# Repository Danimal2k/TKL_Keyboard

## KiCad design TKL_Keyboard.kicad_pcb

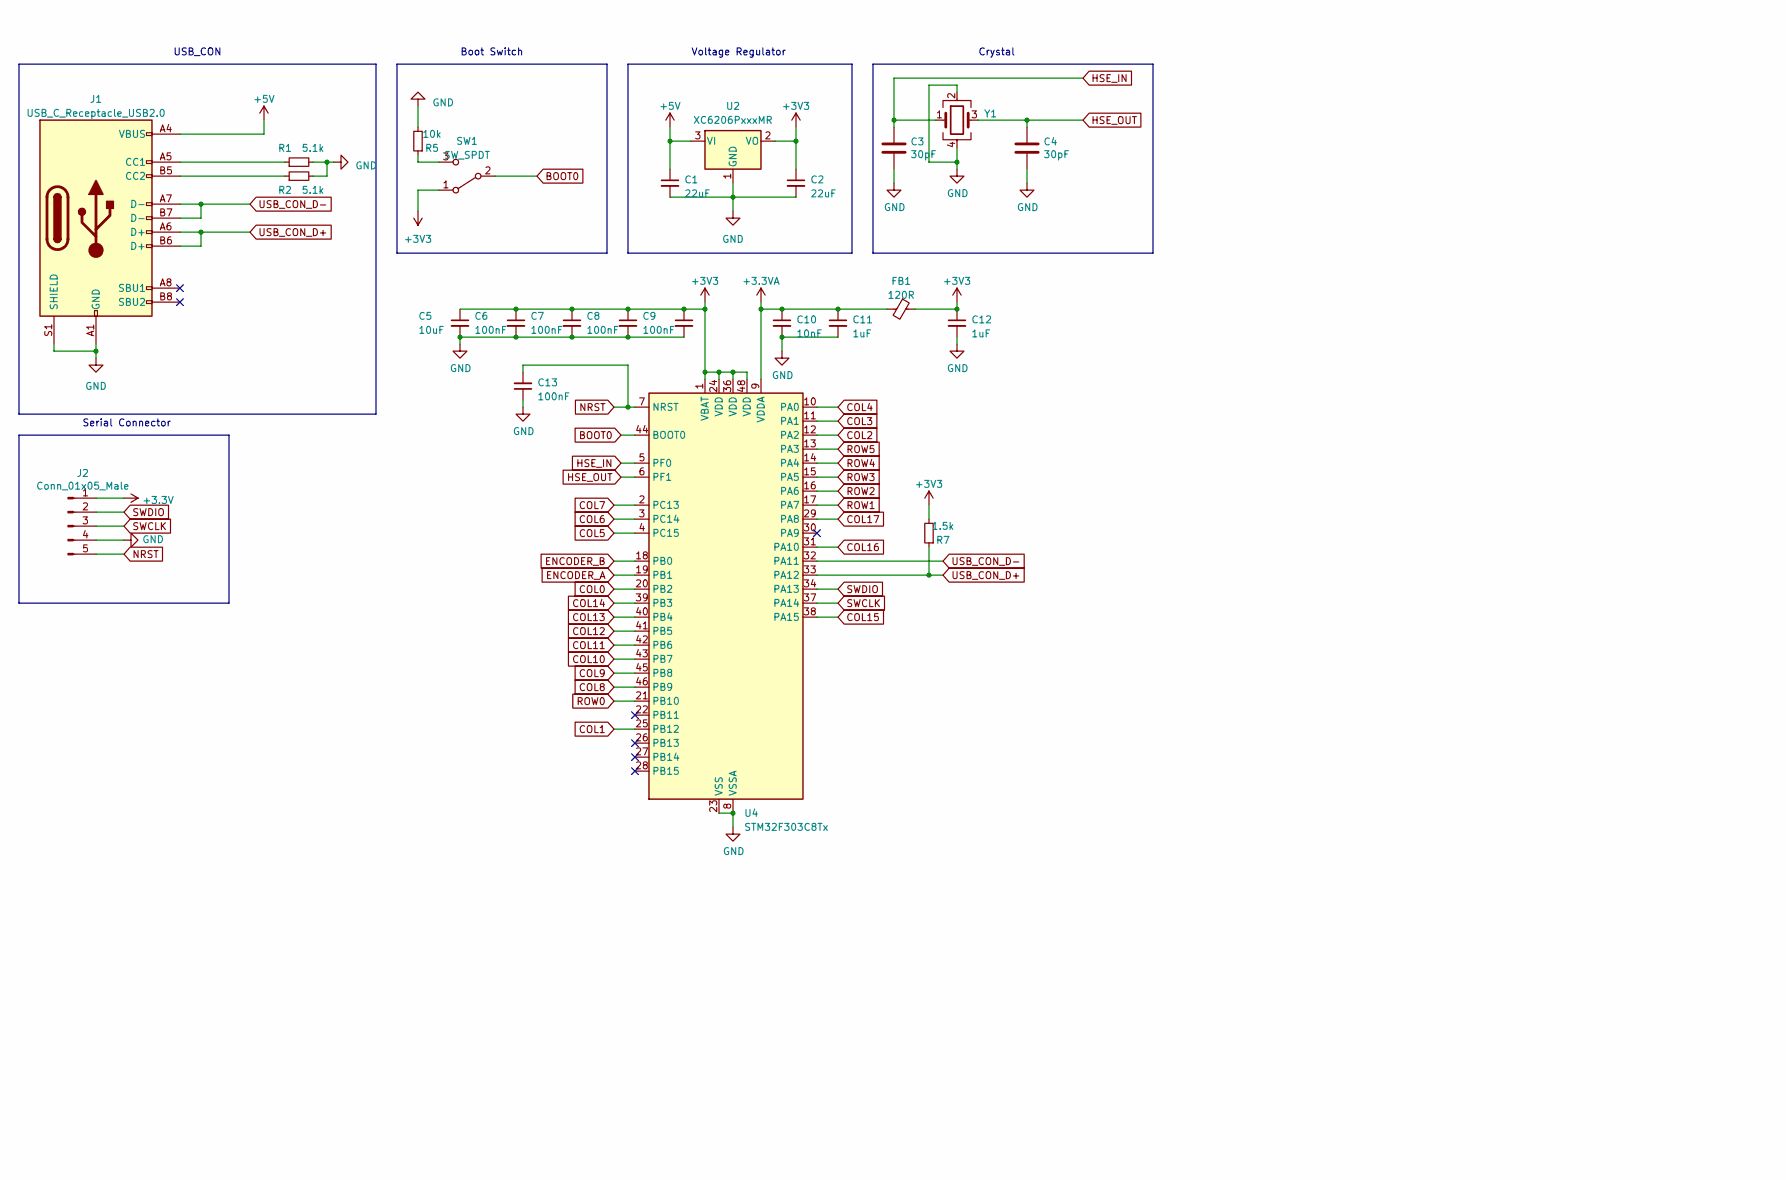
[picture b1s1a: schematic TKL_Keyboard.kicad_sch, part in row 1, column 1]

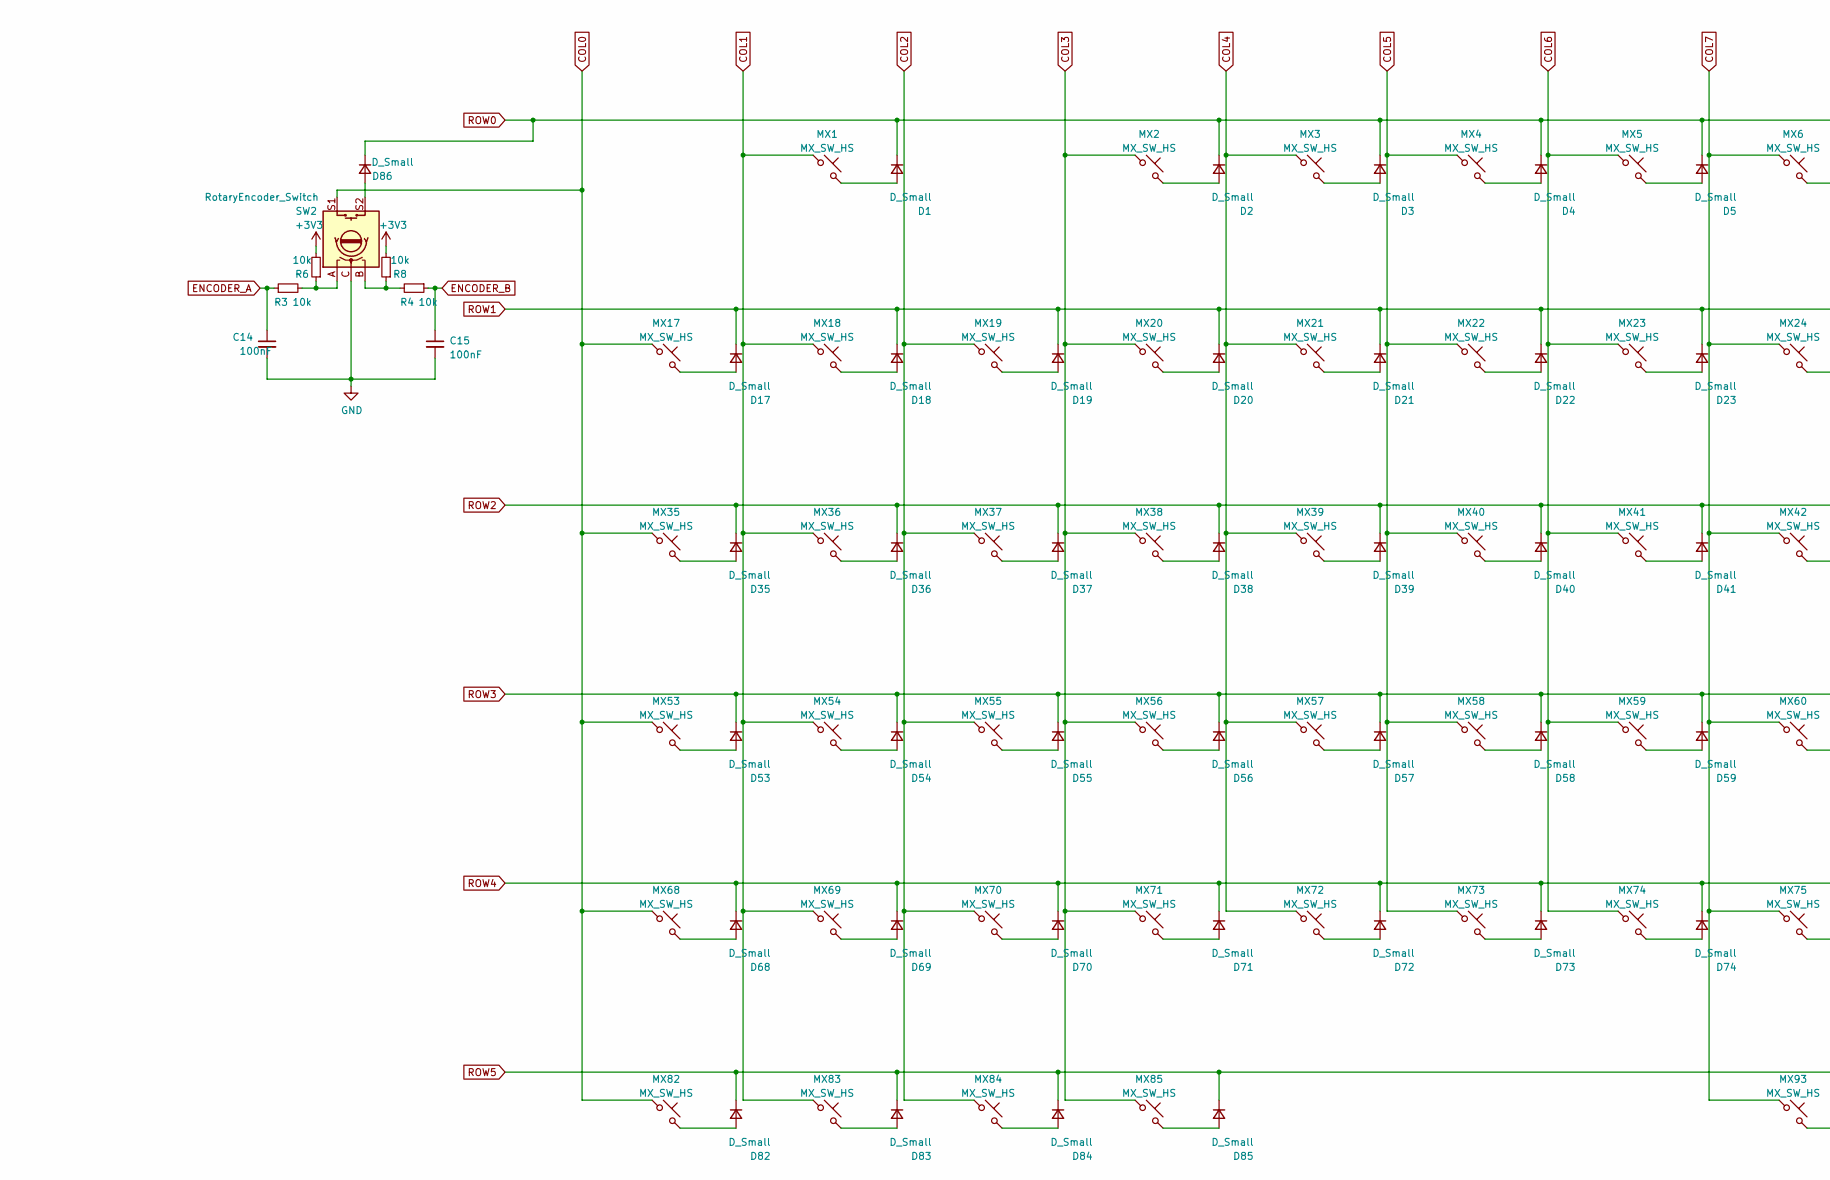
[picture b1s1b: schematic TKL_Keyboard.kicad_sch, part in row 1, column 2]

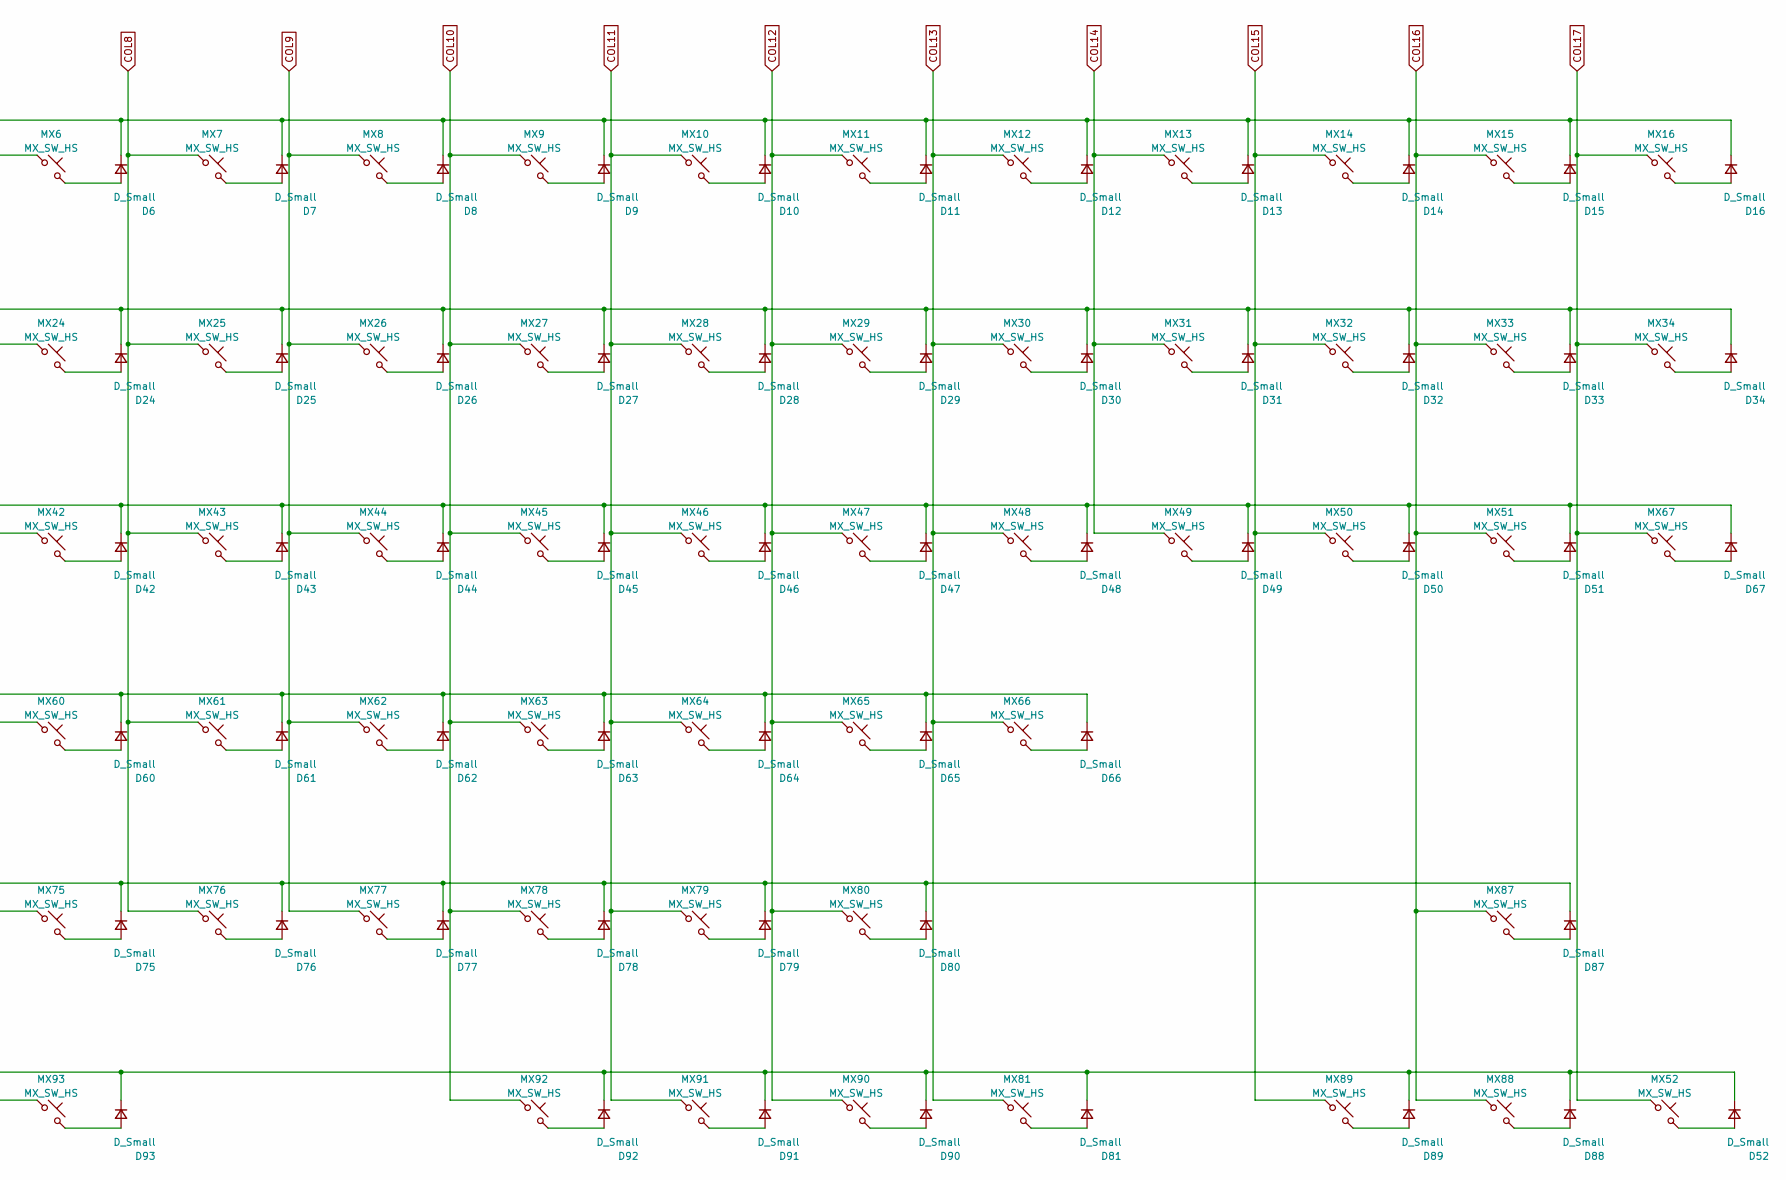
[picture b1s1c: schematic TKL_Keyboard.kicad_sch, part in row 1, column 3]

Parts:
C1, C2: 22uF; C_0805_2012Metric
C3, C4: 30pF; C_0402_1005Metric; LCSC PN C22397
C5: 10uF; C_0805_2012Metric
C6, C7, C8, C9, C13, C14, C15: 100nF; C_0402_1005Metric
C10: 10nF; C_0402_1005Metric
C11, C12: 1uF; C_0402_1005Metric
D1, D2, D3, D4, D5, D6, D7, D8, D9, D10, D11, D12, D13, D14, D15, D16, D17, D18, D19, D20, D21, D22, D23, D24, D25, D26, D27, D28, D29, D30, D31, D32, D33, D34, D35, D36, D37, D38, D39, D40, D41, D42, D43, D44, D45, D46, D47, D48, D49, D50, D51, D52, D53, D54, D55, D56, D57, D58, D59, D60, D61, D62, D63, D64, D65, D66, D67, D68, D69, D70, D71, D72, D73, D74, D75, D76, D77, D78, D79, D80, D81, D82, D83, D84, D85, D86, D87, D88, D89, D90, D91, D92, D93: D_Small; D_SOD-123
FB1: 120R; L_0603_1608Metric
J1: USB_C_Receptacle_USB2.0; USB_C_Receptacle_GCT_USB4085_CUSTOM
J2: Conn_01x05_Male; PinHeader_1x05_P2.54mm_Vertical
MX1, MX2, MX3, MX4, MX5, MX6, MX7, MX8, MX9, MX10, MX11, MX12, MX13, MX14, MX15, MX16, MX17, MX18, MX19, MX20, MX21, MX22, MX23, MX24, MX25, MX26, MX27, MX28, MX29, MX30, MX32, MX33, MX34, MX35, MX36, MX37, MX38, MX39, MX40, MX41, MX42, MX43, MX44, MX45, MX46, MX47, MX48, MX49, MX50, MX51, MX52, MX53, MX54, MX55, MX56, MX57, MX58, MX59, MX60, MX61, MX62, MX63, MX64, MX65, MX67, MX68, MX70, MX71, MX72, MX73, MX74, MX75, MX76, MX77, MX78, MX79, MX81, MX82, MX83, MX84, MX85, MX87, MX88, MX89, MX90, MX91, MX92: MX_SW_HS; MXOnly-1U-Hotswap
MX31: MX_SW_HS; MXOnly-2U-Hotswap
MX66, MX69: MX_SW_HS; MXOnly-2.25U-Hotswap
MX80: MX_SW_HS; MXOnly-2.75U-Hotswap
MX93: MX_SW_HS; MXOnly-6.25U-Hotswap-ReversedStabilizers
R1, R2: 5.1k; R_0805_2012Metric
R3, R4, R5, R6, R8: 10k; R_0805_2012Metric
R7: 1.5k; R_0805_2012Metric
SW1: SW_SPDT; SW_SPDT_PCM12
SW2: RotaryEncoder_Switch; RotaryEncoder_Alps_EC11E-Switch_Vertical_H20mm
U2: XC6206PxxxMR; SOT-23-3
U4: STM32F303C8Tx; LQFP-48_7x7mm_P0.5mm
Y1: 16MHz; Crystal_SMD_5032-4Pin_5.0x3.2mm; LCSC PN C133333

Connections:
+3.3VA: C10.1, C11.1, FB1.2, U4.9 (VDDA)
+5V: C1.1, J1.A4 (VBUS), J1.A9 (VBUS), J1.B4 (VBUS), J1.B9 (VBUS), U2.3 (VI)
BOOT0: SW1.2 (B), U4.44 (BOOT0)
COL0: MX17.1, MX35.1, MX53.1, MX68.1, MX82.1, SW2.S1, U4.20 (PB2)
COL1: MX1.1, MX18.1, MX36.1, MX54.1, MX69.1, MX83.1, U4.25 (PB12)
COL2: MX19.1, MX37.1, MX55.1, MX70.1, MX84.1, U4.12 (PA2)
COL3: MX2.1, MX20.1, MX38.1, MX56.1, MX71.1, MX85.1, U4.11 (PA1)
COL4: MX3.1, MX21.1, MX39.1, MX57.1, MX72.1, U4.10 (PA0)
COL5: MX4.1, MX22.1, MX40.1, MX58.1, MX73.1, U4.4 (PC15)
COL6: MX5.1, MX23.1, MX41.1, MX59.1, MX74.1, U4.3 (PC14)
COL7: MX6.1, MX24.1, MX42.1, MX60.1, MX75.1, MX93.1, U4.2 (PC13)
COL8: MX7.1, MX25.1, MX43.1, MX61.1, MX76.1, U4.46 (PB9)
COL9: MX8.1, MX26.1, MX44.1, MX62.1, MX77.1, U4.45 (PB8)
COL10: MX9.1, MX27.1, MX45.1, MX63.1, MX78.1, MX92.1, U4.43 (PB7)
COL11: MX10.1, MX28.1, MX46.1, MX64.1, MX79.1, MX91.1, U4.42 (PB6)
COL12: MX11.1, MX29.1, MX47.1, MX65.1, MX80.1, MX90.1, U4.41 (PB5)
COL13: MX12.1, MX30.1, MX48.1, MX66.1, MX81.1, U4.40 (PB4)
COL14: MX13.1, MX31.1, MX49.1, U4.39 (PB3)
COL15: MX14.1, MX32.1, MX50.1, MX89.1, U4.38 (PA15)
COL16: MX15.1, MX33.1, MX51.1, MX87.1, MX88.1, U4.31 (PA10)
COL17: MX16.1, MX34.1, MX52.1, MX67.1, U4.29 (PA8)
ENCODER_A: C14.1, R3.1, U4.19 (PB1)
ENCODER_B: C15.1, R4.1, U4.18 (PB0)
GND: C1.2, C2.2, C3.2, C4.2, C5.2, C6.2, C7.2, C8.2, C9.2, C10.2, C11.2, C12.2, C13.1, C14.2, C15.2, J1.A1 (GND), J1.A12 (GND), J1.B1 (GND), J1.B12 (GND), J1.S1 (SHIELD), J2.4, R1.2, R2.2, R5.2, SW2.C, U2.1 (GND), U4.8 (VSSA), U4.23 (VSS), U4.35 (VSS), U4.47 (VSS), Y1.2, Y1.4
HSE_IN: C3.1, U4.5 (PF0), Y1.1
HSE_OUT: C4.1, U4.6 (PF1), Y1.3
NRST: C13.2, J2.5, U4.7 (NRST)
unnamed: D1.2 (A), MX1.2
unnamed: D2.2 (A), MX2.2
unnamed: D3.2 (A), MX3.2
unnamed: D4.2 (A), MX4.2
unnamed: D5.2 (A), MX5.2
unnamed: D6.2 (A), MX6.2
unnamed: D7.2 (A), MX7.2
unnamed: D8.2 (A), MX8.2
unnamed: D9.2 (A), MX9.2
unnamed: D10.2 (A), MX10.2
unnamed: D11.2 (A), MX11.2
unnamed: D12.2 (A), MX12.2
unnamed: D13.2 (A), MX13.2
unnamed: D14.2 (A), MX14.2
unnamed: D15.2 (A), MX15.2
unnamed: D16.2 (A), MX16.2
unnamed: D17.2 (A), MX17.2
unnamed: D18.2 (A), MX18.2
unnamed: D19.2 (A), MX19.2
unnamed: D20.2 (A), MX20.2
unnamed: D21.2 (A), MX21.2
unnamed: D22.2 (A), MX22.2
unnamed: D23.2 (A), MX23.2
unnamed: D24.2 (A), MX24.2
unnamed: D25.2 (A), MX25.2
unnamed: D26.2 (A), MX26.2
unnamed: D27.2 (A), MX27.2
unnamed: D28.2 (A), MX28.2
unnamed: D29.2 (A), MX29.2
unnamed: D30.2 (A), MX30.2
unnamed: D31.2 (A), MX31.2
unnamed: D32.2 (A), MX32.2
unnamed: D33.2 (A), MX33.2
unnamed: D34.2 (A), MX34.2
unnamed: D35.2 (A), MX35.2
unnamed: D36.2 (A), MX36.2
unnamed: D37.2 (A), MX37.2
unnamed: D38.2 (A), MX38.2
unnamed: D39.2 (A), MX39.2
unnamed: D40.2 (A), MX40.2
unnamed: D41.2 (A), MX41.2
unnamed: D42.2 (A), MX42.2
unnamed: D43.2 (A), MX43.2
unnamed: D44.2 (A), MX44.2
unnamed: D45.2 (A), MX45.2
unnamed: D46.2 (A), MX46.2
unnamed: D47.2 (A), MX47.2
unnamed: D48.2 (A), MX48.2
unnamed: D49.2 (A), MX49.2
unnamed: D50.2 (A), MX50.2
unnamed: D51.2 (A), MX51.2
unnamed: D52.2 (A), MX52.2
unnamed: D53.2 (A), MX53.2
unnamed: D54.2 (A), MX54.2
unnamed: D55.2 (A), MX55.2
unnamed: D56.2 (A), MX56.2
unnamed: D57.2 (A), MX57.2
unnamed: D58.2 (A), MX58.2
unnamed: D59.2 (A), MX59.2
unnamed: D60.2 (A), MX60.2
unnamed: D61.2 (A), MX61.2
unnamed: D62.2 (A), MX62.2
unnamed: D63.2 (A), MX63.2
unnamed: D64.2 (A), MX64.2
unnamed: D65.2 (A), MX65.2
unnamed: D66.2 (A), MX66.2
unnamed: D67.2 (A), MX67.2
unnamed: D68.2 (A), MX68.2
unnamed: D69.2 (A), MX69.2
unnamed: D70.2 (A), MX70.2
unnamed: D71.2 (A), MX71.2
unnamed: D72.2 (A), MX72.2
unnamed: D73.2 (A), MX73.2
unnamed: D74.2 (A), MX74.2
unnamed: D75.2 (A), MX75.2
unnamed: D76.2 (A), MX76.2
unnamed: D77.2 (A), MX77.2
unnamed: D78.2 (A), MX78.2
unnamed: D79.2 (A), MX79.2
unnamed: D80.2 (A), MX80.2
unnamed: D81.2 (A), MX81.2
unnamed: D82.2 (A), MX82.2
unnamed: D83.2 (A), MX83.2
unnamed: D84.2 (A), MX84.2
unnamed: D85.2 (A), MX85.2
unnamed: D86.2 (A), SW2.S2
unnamed: D87.2 (A), MX87.2
unnamed: D88.2 (A), MX88.2
unnamed: D89.2 (A), MX89.2
unnamed: D90.2 (A), MX90.2
unnamed: D91.2 (A), MX91.2
unnamed: D92.2 (A), MX92.2
unnamed: D93.2 (A), MX93.2
unnamed: J1.A5 (CC1), R1.1
unnamed: J1.B5 (CC2), R2.1
unnamed: R3.2, R6.1, SW2.A
unnamed: R4.2, R8.1, SW2.B
unnamed: R5.1, SW1.3 (C)
ROW0: D1.1 (K), D2.1 (K), D3.1 (K), D4.1 (K), D5.1 (K), D6.1 (K), D7.1 (K), D8.1 (K), D9.1 (K), D10.1 (K), D11.1 (K), D12.1 (K), D13.1 (K), D14.1 (K), D15.1 (K), D16.1 (K), D86.1 (K), U4.21 (PB10)
ROW1: D17.1 (K), D18.1 (K), D19.1 (K), D20.1 (K), D21.1 (K), D22.1 (K), D23.1 (K), D24.1 (K), D25.1 (K), D26.1 (K), D27.1 (K), D28.1 (K), D29.1 (K), D30.1 (K), D31.1 (K), D32.1 (K), D33.1 (K), D34.1 (K), U4.17 (PA7)
ROW2: D35.1 (K), D36.1 (K), D37.1 (K), D38.1 (K), D39.1 (K), D40.1 (K), D41.1 (K), D42.1 (K), D43.1 (K), D44.1 (K), D45.1 (K), D46.1 (K), D47.1 (K), D48.1 (K), D49.1 (K), D50.1 (K), D51.1 (K), D67.1 (K), U4.16 (PA6)
ROW3: D53.1 (K), D54.1 (K), D55.1 (K), D56.1 (K), D57.1 (K), D58.1 (K), D59.1 (K), D60.1 (K), D61.1 (K), D62.1 (K), D63.1 (K), D64.1 (K), D65.1 (K), D66.1 (K), U4.15 (PA5)
ROW4: D68.1 (K), D69.1 (K), D70.1 (K), D71.1 (K), D72.1 (K), D73.1 (K), D74.1 (K), D75.1 (K), D76.1 (K), D77.1 (K), D78.1 (K), D79.1 (K), D80.1 (K), D87.1 (K), U4.14 (PA4)
ROW5: D52.1 (K), D81.1 (K), D82.1 (K), D83.1 (K), D84.1 (K), D85.1 (K), D88.1 (K), D89.1 (K), D90.1 (K), D91.1 (K), D92.1 (K), D93.1 (K), U4.13 (PA3)
SWCLK: J2.3, U4.37 (PA14)
SWDIO: J2.2, U4.34 (PA13)
USB_CON_D+: J1.A6 (D+), J1.B6 (D+), R7.1, U4.33 (PA12)
USB_CON_D-: J1.A7 (D-), J1.B7 (D-), U4.32 (PA11)

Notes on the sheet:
Boot Switch
Crystal
Voltage Regulator
USB_CON
Serial Connector

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
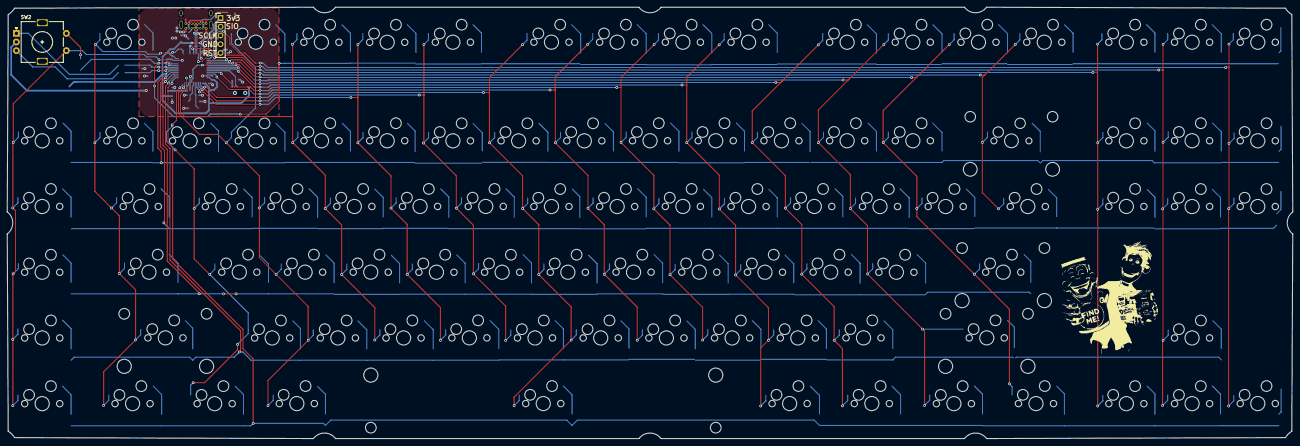
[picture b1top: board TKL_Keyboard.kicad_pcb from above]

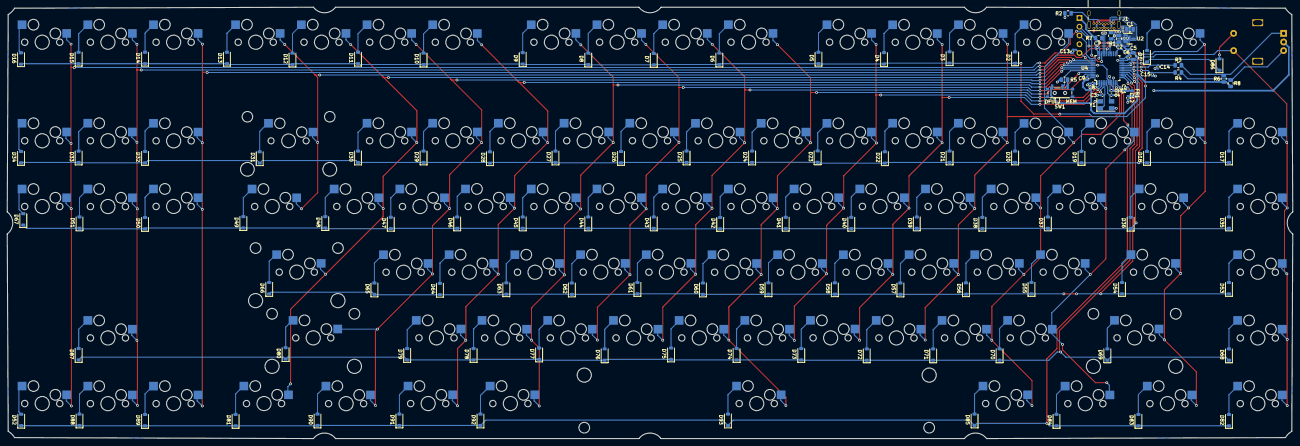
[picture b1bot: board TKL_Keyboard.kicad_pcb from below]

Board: 2 copper layers, 372.7 x 125.0 mm, 216 parts (122 on the bottom side), 136 nets.

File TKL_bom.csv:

Comment,Designator,Footprint
MX_SW_HS,"MX71,MX45,MX41,MX92,MX3,MX77,MX73,MX68,MX26,MX8,MX89,MX10,MX50,MX18,MX42,MX55,MX61,MX79,MX52,MX6,MX49,MX44,MX17,MX82,MX25,MX34,MX13,MX43,MX56,MX4,MX81,MX37,MX59,MX35,MX88,MX48,MX36,MX75,MX54,MX19,MX29,MX85,MX2,MX47,MX16,MX5,MX83,MX30,MX74,MX1,MX67,MX32,MX78,MX87,MX51,MX76,MX14,MX62,MX12,MX64,MX70,MX90,MX11,MX84,MX9,MX21,MX53,MX27,MX72,MX38,MX91,MX39,MX63,MX65,MX28,MX23,MX46,MX20,MX60,MX33,MX24,MX57,MX58,MX40,MX15,MX7,MX22",MXOnly-1U-Hotswap
MX_SW_HS,MX93,MXOnly-6.25U-Hotswap-ReversedStabilizers
Conn_01x05_Male,J2,PinHeader_1x05_P2.54mm_Vertical
MX_SW_HS,MX80,MXOnly-2.75U-Hotswap
RotaryEncoder_Switch,SW2,RotaryEncoder_Alps_EC11E-Switch_Vertical_H20mm
MX_SW_HS,"MX66,MX69",MXOnly-2.25U-Hotswap
MX_SW_HS,MX31,MXOnly-2U-Hotswap
1uF,"C11,C12",C_0402_1005Metric
D_Small,"D18,D63,D46,D89,D23,D41,D34,D38,D67,D65,D74,D87,D84,D22,D69,D77,D24,D27,D3,D37,D17,D52,D42,D90,D58,D93,D53,D6,D20,D12,D72,D39,D44,D92,D86,D51,D16,D35,D57,D15,D28,D7,D47,D11,D85,D73,D79,D56,D29,D88,D26,D55,D31,D76,D9,D49,D45,D70,D59,D78,D81,D10,D83,D75,D30,D66,D48,D60,D33,D64,D62,D21,D36,D5,D1,D71,D68,D32,D61,D2,D82,D14,D4,D8,D19,D43,D80,D50,D13,D25,D40,D54,D91",D_SOD-123
USB_C_Receptacle_USB2.0,J1,USB_C_Receptacle_GCT_USB4085_CUSTOM
10k,"R4,R5,R6,R3,R8",R_0805_2012Metric
100nF,"C13,C15,C14,C8,C6,C9,C7",C_0402_1005Metric
5.1k,"R1,R2",R_0805_2012Metric
XC6206PxxxMR,U2,SOT-23-3
120R,FB1,L_0603_1608Metric
16MHz,Y1,Crystal_SMD_5032-4Pin_5.0x3.2mm
22uF,"C2,C1",C_0805_2012Metric
10uF,C5,C_0805_2012Metric
10nF,C10,C_0402_1005Metric
30pF,"C4,C3",C_0402_1005Metric
SW_SPDT,SW1,SW_SPDT_PCM12
1.5k,R7,R_0805_2012Metric
STM32F303C8Tx,U4,LQFP-48_7x7mm_P0.5mm

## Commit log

2023-08-03 small changes
    Small Changes
    Small Changes
    Small Changes
    Small Changes
    Small Changes
    small changes
2023-08-03 via json
2023-08-12 Firmware
